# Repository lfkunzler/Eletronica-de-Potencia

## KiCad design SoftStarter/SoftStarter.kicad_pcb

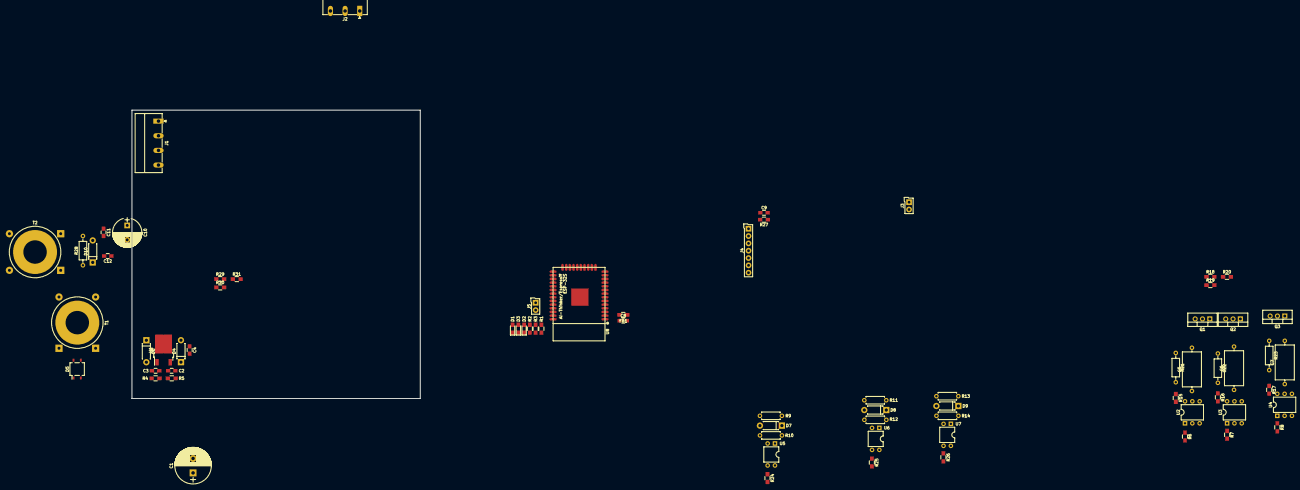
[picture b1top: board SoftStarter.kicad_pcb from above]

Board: 2 copper layers, 100.0 x 100.0 mm, 72 parts (0 on the bottom side), 56 nets, no tracks yet.

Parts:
C1: 220uF; CP_Radial_D12.5mm_P5.00mm
C2, C8, C9, C11: 100nF; C_0805_HandSoldering
C3, C4, C12: 10uF; C_0805_HandSoldering
C5, C6, C7: 22nF; C_Axial_L12.0mm_D6.5mm_P15.00mm_Horizontal
C10: 47uF; CP_Radial_D10.0mm_P5.00mm
D1, D2, D3: LED; LED_0805_HandSoldering
D4, D6, D7, D8, D9: 1N4007; D_DO-41_SOD81_P7.62mm_Horizontal
D5: D_Bridge_+-AA; Diode_Bridge_TO-269AA
D10: 3v3@1W; D_DO-41_SOD81_P7.62mm_Horizontal
FB1: Ferrite_Bead; L_0805_HandSoldering
J1: Conn_01x04_Female; PhoenixContact_MC-G_04x5.08mm_Angled
J2: Conn_01x03_Female; PhoenixContact_MC-G_03x5.08mm_Angled
J3: Conn_01x02_Male; SL-102-X-XX_1x02
J4: JTAG; SL-107-X-XX_1x07
J5: Conn_01x02_Female; SL-102-X-XX_1x02
Q1, Q2, Q3: BT136-500; TO-220-3_Vertical
R1, R2, R3: 180R; R_0805_HandSoldering
R4, R16, R18, R20: 390R; R_0805_HandSoldering
R5: 240R; R_0805_HandSoldering
R6, R7, R8: 470R; R_0805_HandSoldering
R9, R10, R11, R12, R13, R14: 10k@1/3W; R_Axial_DIN0207_L6.3mm_D2.5mm_P7.62mm_Horizontal
R15, R17, R19: 150R; R_0805_HandSoldering
R21, R22, R23: 47R@1W; R_Axial_DIN0207_L6.3mm_D2.5mm_P10.16mm_Horizontal
R24, R25, R26, R27: 10k; R_0805_HandSoldering
R28: 33R@1W; R_Axial_DIN0207_L6.3mm_D2.5mm_P10.16mm_Horizontal
R29, R30: 15k; R_0805_HandSoldering
R31: 1k; R_0805_HandSoldering
T1: Trafo_20P_1S; Transformer_Toroid_Horizontal_D18.0mm
T2: Current Transformer; Transformer_Toroid_Horizontal_D18.0mm
U1: LM317_3PinPackage; TO-252-2
U2, U3, U4: MOC3023; DIP-6_W7.62mm
U5, U6, U7: PC817; DIP-4_W7.62mm
U8: ESP32S; ESP-32S

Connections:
+12V: C1.1, C2.1, D4.1, D5.1, U1.3
/CrossZero_R: R24.1, U5.3, U8.26
/CrossZero_S: R25.1, U6.3, U8.27
/CrossZero_T: R26.1, U7.3, U8.28
/R: J1.3, Q2.2, R9.2, R21.1, T1.1
/RXD0: J5.1, U8.34
/R_CARGA: J2.1, T2.2
/S: J1.2, Q3.2, R11.2, R22.1
/S_CARGA: C6.2, J2.2, Q3.1, R18.1
/T: J1.1, Q1.2, R13.2, R23.1
/TCK: J4.5, U8.16
/TDI: J4.3, U8.14
/TDO: J4.6, U8.23
/TMS: J4.2, U8.13
/TRST: C9.2, J4.1, R27.2, U8.3
/TXD0: J5.2, U8.35
/T_CARGA: C7.2, J2.3, Q1.1, R20.1
/chav_R: R6.2, U8.29
/chav_S: R7.2, U8.30
/chav_T: R8.2, U8.31
/correnteR: C12.1, R31.1, U8.6
/ldConectado: R2.1, U8.33
/ldOn: R1.1, U8.37
/ldSobreCorrente: R3.1, U8.36
GND: C1.2, C2.2, C3.2, C4.2, C8.2, C9.1, C10.2, C11.2, C12.2, D5.2, D10.2, J3.2, J4.4, R4.2, R24.2, R25.2, R26.2, R29.2, U2.2, U3.2, U4.2, U8.1, U8.15, U8.38, U8.39
NEUT: J1.4, R10.2, R12.2, R14.2, T1.2
unnamed: C3.1, D6.2, R4.1, R5.2, U1.1
unnamed: C5.1, R15.1, R21.2
unnamed: C5.2, Q2.1, R16.1, T2.1
unnamed: C6.1, R17.1, R22.2
unnamed: C7.1, R19.1, R23.2
unnamed: C8.1, FB1.2, U8.2
unnamed: C10.1, C11.1, R28.2, R29.1, R30.2, T2.3
unnamed: D1.1, R1.2
unnamed: D2.1, R2.2
unnamed: D3.1, R3.2
unnamed: D5.3, T1.3
unnamed: D5.4, T1.4
unnamed: D7.1, R9.1, U5.1
unnamed: D7.2, R10.1, U5.2
unnamed: D8.1, R11.1, U6.1
unnamed: D8.2, R12.1, U6.2
unnamed: D9.1, R13.1, U7.1
unnamed: D9.2, R14.1, U7.2
unnamed: D10.1, R28.1, R31.2, T2.4
unnamed: J3.1, U8.25
unnamed: Q1.3, R20.2, U4.4
unnamed: Q2.3, R16.2, U2.4
unnamed: Q3.3, R18.2, U3.4
unnamed: R6.1, U2.1
unnamed: R7.1, U3.1
unnamed: R8.1, U4.1
unnamed: R15.2, U2.6
unnamed: R17.2, U3.6
unnamed: R19.2, U4.6
VCC: C4.1, D1.2, D2.2, D3.2, D4.2, D6.1, FB1.1, J4.7, R5.1, R27.1, R30.1, U1.2, U5.4, U6.4, U7.4

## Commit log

2019-04-09 vaaaaaai
2019-04-19 fim do esquema
2019-04-28 fim do esquema, revisado
2019-06-29 interrupcoes timer
2019-06-30 ligando a lampada em 100
2019-07-05 lampada ligando
2019-07-06 acionamento ok
2019-07-07 soft mono ok
2019-07-08 finalizada
2019-07-08 correcao no menu
    lendo a configuracao corretamente
